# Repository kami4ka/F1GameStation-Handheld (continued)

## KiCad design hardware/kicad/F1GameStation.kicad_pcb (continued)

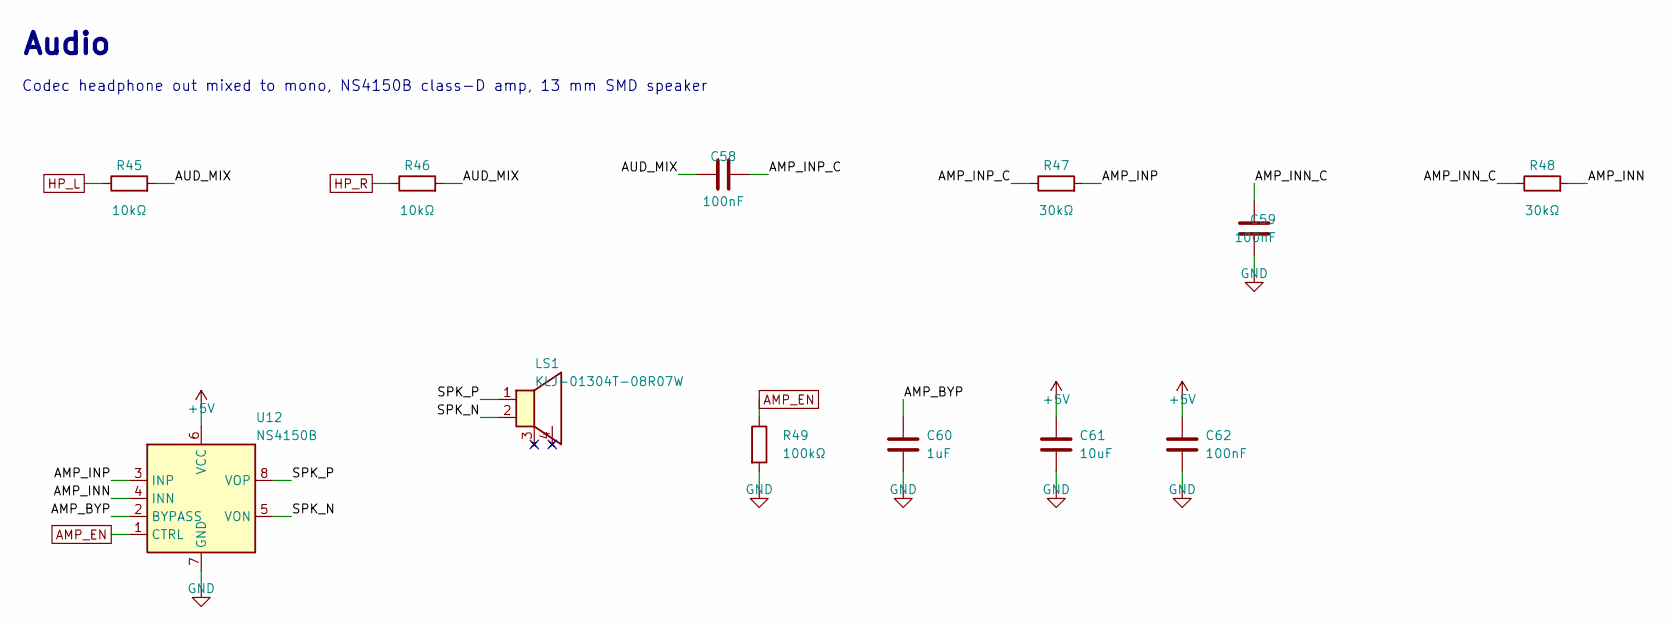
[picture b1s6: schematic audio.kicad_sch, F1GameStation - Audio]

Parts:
C58, C59, C62: 100nF; C_0603_1608Metric; Manufacturer Part CL10B104KB8NNNC; LCSC C1591
C60: 1uF; C_0603_1608Metric; Manufacturer Part CL10B105KA8NNNC; LCSC C29936
C61: 10uF; C_0805_2012Metric; Manufacturer Part CL21A106KAYNNNE; LCSC C15850
LS1: KLJ-01304T-08R07W; Manufacturer Part KLJ-01304T-08R07W; LCSC C18186315
R45, R46: 10kΩ; R_0603_1608Metric; Manufacturer Part 0603WAF1002T5E; LCSC C25804
R47, R48: 30kΩ; R_0603_1608Metric; Manufacturer Part 0603WAF3002T5E; LCSC C22984
R49: 100kΩ; R_0603_1608Metric; Manufacturer Part 0603WAF1003T5E; LCSC C25803
U12: NS4150B; MSOP-8_3x3mm_P0.65mm; Manufacturer Part NS4150B; LCSC C189961

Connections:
+5V: C61.1, C62.1, U12.6 (VCC); also elsewhere on the board
/Audio/AMP_BYP: C60.1, U12.2 (BYPASS)
/Audio/AMP_INN: R48.2, U12.4 (INN)
/Audio/AMP_INN_C: C59.2, R48.1
/Audio/AMP_INP: R47.2, U12.3 (INP)
/Audio/AMP_INP_C: C58.2, R47.1
/Audio/AUD_MIX: C58.1, R45.2, R46.2
/Audio/SPK_N: LS1.2 (-), U12.5 (VON)
/Audio/SPK_P: LS1.1 (+), U12.8 (VOP)
AMP_EN: R49.1, U12.1 (CTRL); also elsewhere on the board
GND: C59.1, C60.2, C61.2, C62.2, R49.2, U12.7 (GND); also elsewhere on the board
HP_L: R45.1; also elsewhere on the board
HP_R: R46.1; also elsewhere on the board

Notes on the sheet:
Audio
Codec headphone out mixed to mono, NS4150B class-D amp, 13 mm SMD speaker

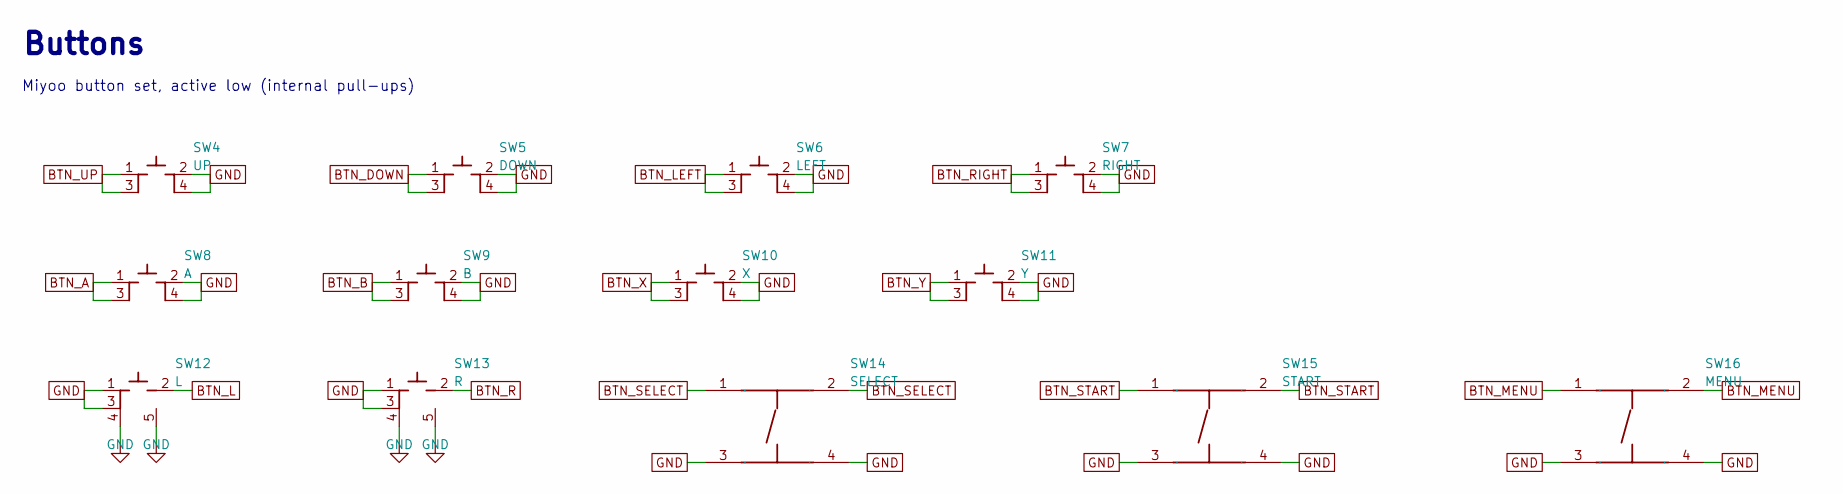
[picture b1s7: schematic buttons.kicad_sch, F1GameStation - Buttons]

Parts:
SW4: UP; SKRRAAE010; Manufacturer Part SKRRAAE010; LCSC C97437
SW5: DOWN; SKRRAAE010; Manufacturer Part SKRRAAE010; LCSC C97437
SW6: LEFT; SKRRAAE010; Manufacturer Part SKRRAAE010; LCSC C97437
SW7: RIGHT; SKRRAAE010; Manufacturer Part SKRRAAE010; LCSC C97437
SW8: A; SKRRAAE010; Manufacturer Part SKRRAAE010; LCSC C97437
SW9: B; SKRRAAE010; Manufacturer Part SKRRAAE010; LCSC C97437
SW10: X; SKRRAAE010; Manufacturer Part SKRRAAE010; LCSC C97437
SW11: Y; SKRRAAE010; Manufacturer Part SKRRAAE010; LCSC C97437
SW12: L; SKRTLAE010; Manufacturer Part SKRTLAE010; LCSC C110293
SW13: R; SKRTLAE010; Manufacturer Part SKRTLAE010; LCSC C110293
SW14: SELECT; SW-SMD_4P-L4.2-W3.4-P2.15-LS5.2; Manufacturer Part SH-1808SN-250gf; LCSC C52092028
SW15: START; SW-SMD_4P-L4.2-W3.4-P2.15-LS5.2; Manufacturer Part SH-1808SN-250gf; LCSC C52092028
SW16: MENU; SW-SMD_4P-L4.2-W3.4-P2.15-LS5.2; Manufacturer Part SH-1808SN-250gf; LCSC C52092028

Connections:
BTN_A: SW8.1, SW8.3; also elsewhere on the board
BTN_B: SW9.1, SW9.3; also elsewhere on the board
BTN_DOWN: SW5.1, SW5.3; also elsewhere on the board
BTN_L: SW12.2; also elsewhere on the board
BTN_LEFT: SW6.1, SW6.3; also elsewhere on the board
BTN_MENU: SW16.1, SW16.2; also elsewhere on the board
BTN_R: SW13.2; also elsewhere on the board
BTN_RIGHT: SW7.1, SW7.3; also elsewhere on the board
BTN_SELECT: SW14.1, SW14.2; also elsewhere on the board
BTN_START: SW15.1, SW15.2; also elsewhere on the board
BTN_UP: SW4.1, SW4.3; also elsewhere on the board
BTN_X: SW10.1, SW10.3; also elsewhere on the board
BTN_Y: SW11.1, SW11.3; also elsewhere on the board
GND: SW4.2, SW4.4, SW5.2, SW5.4, SW6.2, SW6.4, SW7.2, SW7.4, SW8.2, SW8.4, SW9.2, SW9.4, SW10.2, SW10.4, SW11.2, SW11.4, SW12.1, SW12.3, SW12.4, SW12.5, SW13.1, SW13.3, SW13.4, SW13.5, SW14.3, SW14.4, SW15.3, SW15.4, SW16.3, SW16.4; also elsewhere on the board

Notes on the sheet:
Buttons
Miyoo button set, active low (internal pull-ups)

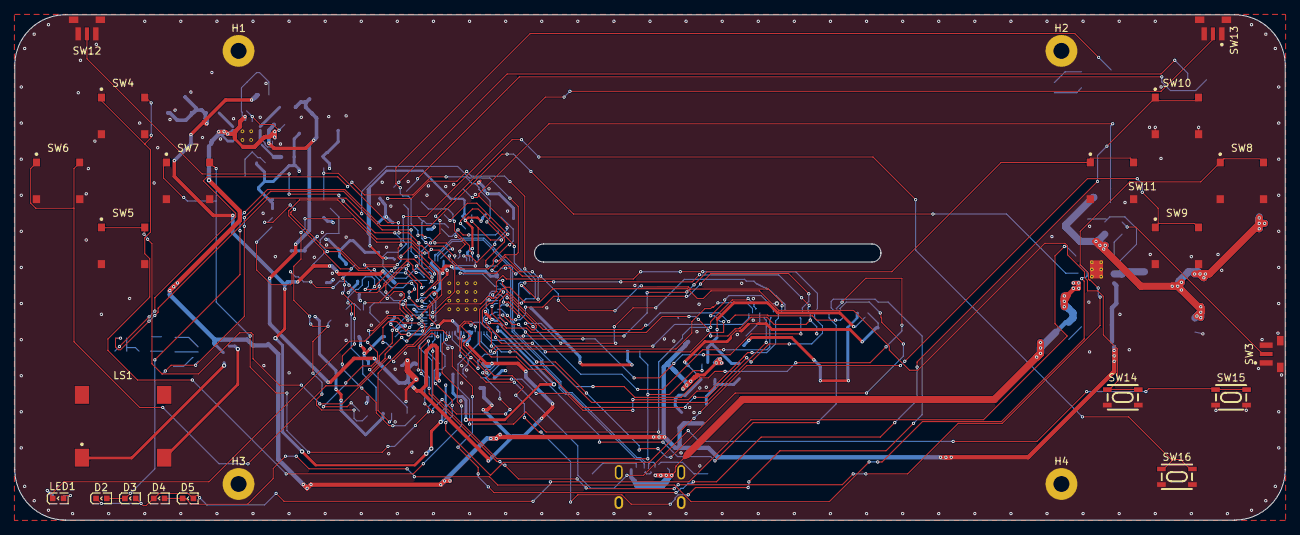
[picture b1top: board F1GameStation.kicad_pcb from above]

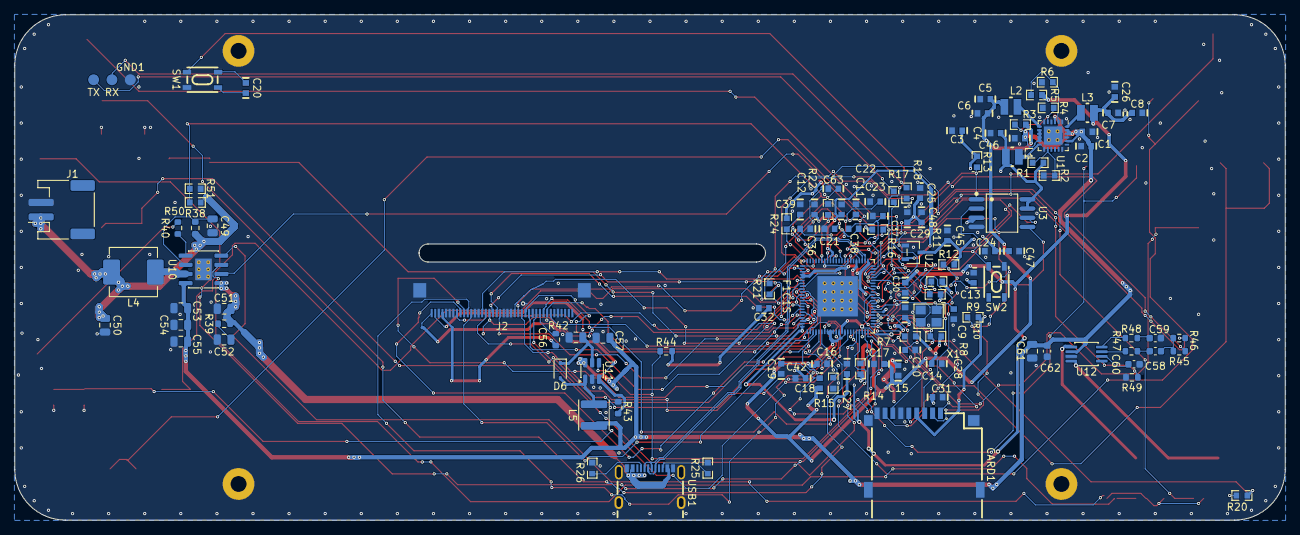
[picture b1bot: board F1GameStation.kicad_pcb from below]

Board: 4 copper layers, 176.0 x 70.0 mm, 141 parts (117 on the bottom side), 106 nets.

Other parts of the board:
BT1: LiPo 606090; LiPo_606090
H1, H2, H3, H4: M2; MountingHole_2.2mm_M2_Pad

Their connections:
GND: H1.1, H2.1, H3.1, H4.1; also elsewhere on the board

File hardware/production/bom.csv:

Designator,Footprint,Quantity,Value,LCSC Part #
"C1, C4, C5, C7, C12, C13, C17, C22, C24, C27, C36, C37, C38, C39, C46, C48",C0603,16,10uF,C380317
"C9, C10",C0603,2,15pF,C1644
"C2, C3, C6, C8, C11, C14, C15, C16, C18, C19, C20, C25, C26, C28, C29, C30, C31, C32, C58, C59, C62, C63",C0603,22,100nF,C1591
"C21, C23, C47, C60",C0603,4,1uF,C29936
C42,C0603,1,100nF,C14663
C45,C0603,1,10uF,C19702
"C49, C50, C53, C54, C55",0805,5,22uF,C45783
"C51, C52, C57, C61",0805,4,10uF,C15850
C56,0805,1,1uF 50V,C91185
CARD1,TF-SMD_TF-PUSH,1,TF PUSH,C393941
"D2, D3, D4, D5, LED1",LED0603-RD_RED,5,XL-1608SURC-06,C965799
D6,D_SOD-323,1,B5819WS,C64886
F1C1S,QFN-88_L10.0-W10.0-P0.40-BL-EP,1,F1C200S-88,C2879851
J1,JST_PH_S2B-PH-SM4-TB_1x02-1MP_P2.00mm_Horizontal,1,BATTERY 1S,C295747
J2,AFC24-S40FIA-00_REV,1,LCD 40P RGB (FPC043CS4001),C262686
"L1, L2, L3",IND-SMD_L2.5-W2.0-B,3,2.2uH,C7471148
L4,L_Changjiang_FXL0630,1,1uH,C167216
L5,L_Sunlord_SWPA4020S,1,22uH,C167838
LS1,KLJ-01304T-08R07W,1,KLJ-01304T-08R07W,C18186315
R1,R0603,1,680kΩ,C137690
"R8, R9, R10, R11, R12, R13, R16",R0603,7,10kΩ,C844918
"R14, R15",R0603,2,2kΩ,C105576
"R17, R18, R20",R0603,3,1kΩ,C2907002
"R2, R4",R0603,2,150kΩ,C114660
R21,R0603,1,22Ω,C2930077
"R22, R50",R0603,2,200kΩ,C105574
R24,R0603,1,0Ω,C54531634
"R25, R26",R0603,2,5.1kΩ,C2907044
R3,R0603,1,470kΩ,C114622
R38,0603,1,0.5Ω,C45312
R39,0603,1,2Ω,C22977
"R40, R42, R44, R45, R46",0603,5,10kΩ,C25804
R43,0603,1,10Ω,C22859
"R47, R48",0603,2,30kΩ,C22984
R49,0603,1,100kΩ,C25803
"R5, R6, R7, R51",R0603,4,100kΩ,C14675
"SW1, SW2, SW14, SW15, SW16",SW-SMD_4P-L4.2-W3.4-P2.15-LS5.2,5,"SH-1808SN-250gf (SH-1808SN-250gf, SELECT, START, MENU)",C52092028
"SW4, SW5, SW6, SW7, SW8, SW9, SW10, SW11",SKRRAAE010,8,"SKRRAAE010 (X, Y, UP, DOWN, LEFT, RIGHT, A, B)",C97437
"SW3, SW12, SW13",SKRTLAE010,3,"SKRTLAE010 (L, R, POWER)",C110293
U1,QFN-24_L4.0-W4.0-P0.50-BL-EP2.6,1,EA3059C,C570858
U10,SOIC-8-1EP_3.9x4.9mm_P1.27mm_EP2.29x3mm_ThermalVias,1,IP5306,C181692
U11,SOT-23-6,1,MP3202DJ-LF-Z-MS,C52988868
U12,MSOP-8_3x3mm_P0.65mm,1,NS4150B,C189961
U2,SOT-23-3_L3.0-W1.7-P0.95-LS2.9-BR,1,XC6206P302MR,C347375
U3,SOIC-8_L5.3-W5.3-P1.27-LS8.0-BL,1,W25Q128JVSIQ,C97521
USB1,USB-C-SMD_TYPE-C-16PIN-2MD-073,1,TYPE-C 16PIN 2MD(073),C2765186
X1,CRYSTAL-SMD_4P-L3.2-W2.5-BL,1,24MHz,C70590
